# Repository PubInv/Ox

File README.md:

# NASA-COG

## Final Report

The final report delivered to NASA for this project can be [read here](https://drive.google.com/file/d/1jfJcSLfsybuC49I7llPhfTNI8ucRUW3h/view?usp=sharing).

## Introduction

This is a repo for a control system made for NASA to drive a Ceramic Oxygen Generation
technology they have developed. It was forked from ["The Ox"]() project of Public Invention run by Mr. Ben Coombs, which was in turn a fork of the VentOS project of Helpful Engineering let my Ben Coombs, Dr. Erich Schulz, and Robert L. Read.

However, the main reason we are starting with this fork is not that the Pressure Swing
Adsorption system of the Ox is a particularly relevant, but rather that the code
represents a nice platform of simple microcontroller control of related machines.

To wit, includes PlatformIO configuration, a state machine (finite automata),
a superloop architecutre, and a hardware abstraction layer.

This particular project of NASA will improve life support technology in space,
but may eventually greatly improve global health.

An unlisted [YouTube video](https://youtu.be/1nq-Mw7jZ5A) has been uploaded that shows this work in progress as of September, 2022.

## How to run

### Linux
The fundamental way to run this is to perform:  
> cd firmware  
> pio run -e native && ./.pio/build/native/program  
We are currently creating the [RibbonFish](https://github.com/PubInv/NASA-COG/blob/develop/RibbonFish.md) proof-of-concept.
This can be run on a Due by executing:  
> make pio-run-due_ribbonfish  
As this develops, it will use a specific Due hardware configuration,  
please see the [documentation](https://github.com/PubInv/NASA-COG/blob/develop/RibbonFish.md) for details to build your own.  

### Windows
With Visual Studio Code.  
Install the Plateform IO extention  
To open he project in Visual Studio Code.  
Open Project. Navigate to the firmware folder.   
Select the file platformio.ini  

## Annoyances

AFAIK, PlatformIO forces a directory tree depth of 5 levels.

This is not enough to organize the Hardware Abstraction Level they way I would prefer, forcing us to make some messy directories that are less than clear.

For example, to implement a Temperature Sensor, we would ideally have an
abstract (or virtual) implementation, a folder for real hardware,
and a folder for mock sensors.  I have no choice now but to jam
the mock sensors into the same directory with the real hardware and
use a naming convnention.

## The Command System

The NASA-COG system needs to allow the user to enter commands. The most obvious of these is "turn off".
Because the system should avoid thermal shocks, this is actually not simple.

We have previously used an [approach](https://github.com/PubInv/PIRCS-pubinv-respiration-control-standard) of using simple JSON objects to represent commands. We propose to use the same idea here, but obviously,
the command will be custom to the NASA-COG.

### Parameter Setting Commands
The general scheme is to use a JSON object like:

```JavaScript
{ "com": "T",
  "par": 7,
  "mod": "T",
  "val" : 732.3
  }
```

1. "com" is the command. For example, "T" can mean "set Temperature".
2. "par" is a parameter used to specify something about how to execute the command. For example, 7 could mean location 7, which might be between the 6th and 7th stack.
3. "mod" is a modifier of the command. For example, the "set Temperature" command could be used to
set the minimum, maximum, or the target temperature.
4. "val" is the value that is to be set.

For this problem space, we can specify some global parameters of the problem, some of which
involve safety. These can of course have default values "hard wired" into the code, but an
experimenter may wish to change these values (carefully).

1. The maximum rate of voltage change applied to a stack. Nominally we have defined this as 1 volt/second.
We have evidence that too rapid a voltage change (such as that caused by pulse-width modulation) can destroy
a stack.
2. The maximum rate of temperature change for a stack. Nominally we may say this as 2 degree K per minute,
which would allow the machine to reach operating temperature in 6 hours.
3. The maximum temperature difference across a stack in any dimenstion. We may not be able to control
this directly, but we can use it as a target.
4. The maximum voltage applied to a stack.
5. The maximum amperage applied to a stack.

### Event-like Commands

We will need other commands that represent discrete events in time. For example, each transition in the
state transition diagram below may be initiated by a command from the user (they may also occur
automatically due to an internal fault or even normal operation.)

We can implement particular commands with the same scheme.

For example, the simple object:

```JavaScript
{ "com": "C",
  "par": 0,
  "int": "s",
  "mod": "U",
  "val" : 0.0
  }
```

Could mean "Cool Down". The value "U" is used becasue the "mod" command is "unusued" in this case.

```JavaScript
{ "com": "W",
  "par": M,
  "int": "s",
  "mod": "U",
  "val" : 0.0
  }
```

In actual practice, these commands will be pasted into the serial port using either PlatformIO or the Arduino IDE.

Eventually, a user interface may be implemented that uses a knob or a nice webpage to enter commands.
However, by having each of these take only actions that can be implemented as such a command,
we bring discipline to the internal code.

## Actual Serial Commands

The serial port currently supports 6 one-character commands: w,c,e,a,i,o.
These mean:
1. warmup
2. cool down
3. emergency shutdown
4. acknowledge
5. idle
6. operate

Note: "acknowledge" means that the operator acknowledges that a critical
state has occurred and asserts it is okay to return to normal operation,
either because the problem as been removed or for some other reason.

Addtionally, the system supports "full commands", that look like this:

> { "com": "W", "par": "M", "int": "s", "mod": "U", "val" : 0.0 }

> { "com": "C", "par": "M", "int": "s", "mod": "U", "val" : 0.0 }

> { "com": "E", "par": "M", "int": "s", "mod": "U", "val" : 0.0 }

> { "com": "A", "par": "M", "int": "s", "mod": "U", "val" : 0.0 }

> { "com": "I", "par": "M", "int": "s", "mod": "U", "val" : 0.0 }

> { "com": "O", "par": "M", "int": "s", "mod": "U", "val" : 0.0 }

In fact, each "one character" command is a short hand for these commands.

The following format can be used to set parameters (P).
The three most important parameters are:
1. T : Temperature (in C) going into the stack
2. C : Current (in milliamps) going into the stack
3. F : Fan speed in RPM (we expect this to change to flow rate in SLM)
> { "com": "P", "par": "T", "int": "T", "mod": "U", "val" : 35 }

> { "com": "P", "par": "C", "int": "T", "mod": "U", "val" : 500 }

> { "com": "P", "par": "F", "int": "T", "mod": "U", "val" : 2000 }

These three commands set the:
1. Temperature into the stack to 35C
2. Set the Target current into the stack to 500 milliamps
3. Set the flow rate to 2000 ml/seconds

## License

In general we intend to follow the [Public Invention Licensed Guidelines](https://github.com/PubInv/PubInv-License-Guidelines) unless
NASA requests something different. If you are starting your own project, please
feel free to fork the license guidelines as a starting point if you like our
license policy.

This program includes free software: you can redistribute it and/or modify it under the terms of the GNU Affero General Public License as published by the Free Software Foundation, either version 3 of the License, or (at your option) any later version.

See the GNU Affero General Public License for more details. You should have received a copy of the GNU Affero General Public License along with this program. If not, see <https://www.gnu.org/licenses/>.

This program is distributed in the hope that it will be useful, but WITHOUT ANY WARRANTY; without even the implied warranty of MERCHANTABILITY or FITNESS FOR A PARTICULAR PURPOSE.

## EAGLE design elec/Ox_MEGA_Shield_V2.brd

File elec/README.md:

# Electrical Information on ODECOS Controler(s) and Plant(s)
PCB Connector Pin signal names, Due Signal Names, Chassis wiring and related information
Inverse cronological order

## Unit 3-???
A place holder for future work
See: TBD

## Unit 2
### Notes for creation of a new PCB  
This table pulls from information in the references 1 and 2.   
References:
1. Due Pin-Out Map for OEDCS1 : https://docs.google.com/spreadsheets/d/18wP1Cyg5-j3FP92x7no_JsCCFNvo9y2avyn5nvmAj6I/edit#gid=0
2. Fan Controller and Fan Wiring for OEDCS1: https://docs.google.com/document/d/1n3v-AxqNKEzcKqmHicGKnFmG8sKbNEL_pGaUlU9CZ8U/edit

   WARNING! At present pin D4 works without an external pull up resistor for the termocouples, but D5 does not; it requires an external pull up resistor
   Until we have time to rework our perf board, I am going to continue to use D4 for the MAX31850 OneWire interface.

#### Due Pin Wiring
| **Due Pin Number** 	| **Breakout** 	| **Signal Name** 	| **Set as I/O**   	| **Connection**                      	| **Notes**                             	|
|--------------------	|--------------	|-----------------	|------------------	|-------------------------------------	|---------------------------------------	|
| D0                 	| J6-2         	| NA              	| Input pullup.    	| None                                	| Not used                              	|
| D1                 	| J6-1         	| NA              	| Input pullup.    	| None                                	| Not used                              	|
| D2                 	| J6-3         	| NA              	| Input pullup.    	| None                                	| Not used                              	|
| D3                 	| J6-4         	| NA              	| Input pullup.    	| None                                	| Not used                              	|
| D4                 	| J6-5         	| SD ENABLE (BUT ALSO TEMP1) | Input pullup.    	| None                      	| SD CS on Ethernet card.               	|
| D5                 	| J6-6         	| TEMP1           	| BiDirection      	| Dallas 1 Wire / MAX31850K           	| Three daisy chained, requires 4.7k ohm pull up resistor (but D4 does not!) Please see note                   	|
| D6                 	| J6-7         	| NA              	| Input pullup.    	| None                                	| Not used                              	|
| D7                 	| J6-8         	| NA              	| Input pullup.    	| None                                	| Not used                              	|
| D8                 	| J7-1         	| NA              	| Input pullup.    	| None                                	| Not used                              	|
| D9                 	| J7-2         	| nFAN1_PWM       	| Output           	| Controlles transistor Q1            	| Was BLOWER_PWM                        	|
| D10                	| J7-3         	| NA              	| Input pullup.    	| None                                	| Not used                              	|
| D11                	| J7-4         	| NA              	| Input pullup.    	| None                                	| Not used                              	|
| D12                	| J7-5         	| NA              	| Input pullup.    	| None                                	| Not used                              	|
| D13                	| J7-6         	| NA              	| Input pullup.    	| None                                	| Not used                              	|
| D13                	| J7-6         	| NA              	| Input pullup.    	| None                                	| Not used                              	|
| D14                	| J2-1         	| NA              	|                  	| None                                	| Not used                              	|
| D15                	| J2-2         	| NA              	| Input pullup.    	| None                                	| Not used                              	|
| D16                	| J2-3         	| NA              	| Input pullup.    	| None                                	| Can be TX2                            	|
| D17                	| J2-4         	| NA              	| Input pullup.    	| None                                	| Can be RX2                            	|
| D18                	| J2-5         	| D_PSU_TX        	| UART1 TX         	| D_PSU_TX, R15 (then to Power Supply 	| TX1                                   	|
| D19                	| J2-6         	| D_PSU_RX        	| UART1 RX         	| D_PSU_RX, R14 (then to Power Supply 	| RX1                                   	|
| D20                	| J2-7         	| SDA             	| SDA              	| test point SDA1, R4, R13            	| SDA                                   	|
| D21                	| J2-8         	| SCL             	| SCL              	| test point SCL1, R2, R16            	| SCL                                   	|
| D22                	| J8-4         	| BLOWER_ENABLE   	| OUTPUT           	| R10                                 	| Enable Switched_Fan_Power at J15 9-12 	|
| D23                	| J8-3         	| NA              	| Input pullup.    	| None                                	| Not used                              	|
| D24                	| J8-6         	| NA              	| Input pullup.    	| None                                	| Not used                              	|
| D25                	| J8-5         	| NA              	| Input pullup.    	| None                                	| Not used                              	|
| D26                	| J8-8         	| NA              	| Input pullup.    	| None                                	| Not used                              	|
| D27                	| J8-7         	| NA              	| Input pullup.    	| None                                	| Not used                              	|
| D28                	| J8-10        	| NA              	| Input pullup.    	| None                                	| Not used                              	|
| D29                	| J8-9         	| NA              	| Input pullup.    	| None                                	| Not used                              	|
| D30                	| J8-12        	| NA              	| Input pullup.    	| None                                	| Not used                              	|
| D31                	| J8-11        	| NA              	| Input pullup.    	| None                                	| Not used                              	|
| D32                	| J8-14        	| nCS_GPAD        	| Output for nCS   	| R55, R61, Q5                        	| on 3.3 Volt                           	|
| D33                	| J8-13        	| TC_nCS1         	| Output for nCS   	| Thermocouple 1, R7                  	| on 3.3 Volt                           	|
| D34                	| J8-16        	| TC_nCS2         	| Output for nCS   	| Thermocouple 2, R3                  	| on 3.3 Volt                           	|
| D35                	| J8-15        	| TC_nCS3         	| Output for nCS   	| Thermocouple 3, R1                  	| on 3.3 Volt                           	|
| D36                	| J8-18        	| NA              	| Input pullup.    	| None                                	| Not used                              	|
| D37                	| J8-17        	| NA              	| Input pullup.    	| None                                	| Not used                              	|
| D38                	| J8-20        	| NA              	| Input pullup.    	| None                                	| Not used                              	|
| D39                	| J8-19        	| NA              	| Input pullup.    	| None                                	| Not used                              	|
| D39                	| J8-19        	| NA              	| Input pullup.    	| None                                	| Not used                              	|
| D40                	| J8-22        	| NA              	| Input pullup.    	| None                                	| Not used                              	|
| D41                	| J8-21        	| NA              	| Input pullup.    	| None                                	| Not used                              	|
| D42                	| J8-24        	| NA              	| Input pullup.    	| None                                	| Not used                              	|
| D43                	| J8-23        	| NA              	| Input pullup.    	| None                                	| Not used                              	|
| D44                	| J8-26        	| NA              	| Input pullup.    	| None                                	| Not used                              	|
| D45                	| J8-25        	| NA              	| Input pullup.    	| None                                	| Not used                              	|
| D46                	| J8-28        	| NA              	| Input pullup.    	| None                                	| Not used                              	|
| D47                	| J8-27        	| NA              	| Input pullup.    	| None                                	| Not used                              	|
| D48                	| J8-30        	| NA              	| Input pullup.    	| None                                	| Not used                              	|
| D49                	| J8-29        	| NA              	| Input pullup.    	| None                                	| Not used                              	|
| D50                	| J8-32        	| NA              	| Input pullup.    	| None                                	| Not used                              	|
| D51                	| J8-31        	| SSR_PWM         	| OUTPUT           	| R9                                  	| Active High.                          	|
| D52                	| J8-34        	| NA              	| Input pullup.    	| None                                	| Not used                              	|
| D53                	| J8-33        	| NA              	| Input pullup.    	| None                                	| Not used                              	|
| SDA1               	| J7-9         	| NA              	| Input pullup.    	| None                                	| Not used                              	|
| SCL1               	| J7-10        	| NA              	| Input pullup.    	| None                                	| Not used                              	|
| CANR               	| J4-7         	| NA              	| Input pullup.    	| None                                	| Not used                              	|
| CANT               	| J4-8         	| NA              	| Input pullup.    	| None                                	| Not used                              	|
| DAC0               	| J4-5         	| Disable         	| Only Output      	| None                                	| Not used                              	|
| DAC1               	| J4-6         	| Disable         	| Only Output      	| None                                	| Not used                              	|
| A0                 	| J5-1         	| BLOWER_TACH     	| Input pullup.    	| R11                                 	| Measure RPM                           	|
| A1                 	| J5-2         	| NA              	| Input pullup.    	| None                                	| Not used                              	|
| A2                 	| J5-3         	| NA              	| Input pullup.    	| None                                	| Not used                              	|
| A3                 	| J5-4         	| NA              	| Input pullup.    	| None                                	| Not used                              	|
| A4                 	| J5-5         	| NA              	| Input pullup.    	| None                                	| Not used                              	|
| A5                 	| J5-6         	| NA              	| Input pullup.    	| None                                	| Not used                              	|
| A6                 	| J5-7         	| NA              	| Input pullup.    	| None                                	| Not used                              	|
| A7                 	| J5-8         	| NA              	| Input pullup.    	| None                                	| Not used                              	|
| A8                 	| J4-1         	| NA              	| Input pullup.    	| None                                	| Not used                              	|
| A9                 	| J4-2         	| NA              	| Input pullup.    	| None                                	| Not used                              	|
| A9                 	| J4-2         	| NA              	| Input pullup.    	| None                                	| Not used                              	|
| A10                	| J4-3         	| NA              	| Input pullup.    	| None                                	| Not used                              	|
| A11                	| J4-4         	| NA              	| Input pullup.    	| None                                	| Not used                              	|
| AREF               	| J7-8         	| NA              	| From DUE         	| None                                	| Not used                              	|
| nRST1              	| J3-6         	| NA              	| Pulled up on DUE 	| None                                	| Not used                              	|
| IOREF              	| J3-7         	| NA              	| NA               	| None                                	| Not used                              	|
| VIN                	| J3-1         	| VIN             	| NA               	| +12V into this pin through R76      	|                                       	|
| +5V                	| J3-4         	| VIN+5V          	| NA               	| Power from Due voltage regulator    	| Three pins.                           	|
| 3.3V               	| J3-5         	| 3.3V            	| NA               	| Power from Due voltage regulator    	| One pin.                              	|
| MISO               	| tp CPIO1     	| CIPO            	| Input            	| SPI bus                             	|                                       	|
| MOSI               	| tp COPI      	| COPI            	| Output           	| SPI bus                             	|                                       	|
| SCK                	| tp SPI_SCK   	| SPI_SCK         	| Output           	| SPI bus                             	|                                       	|
| nRST2              	| NA           	| SPI_nRST        	| Input            	| S1 reset switch                     	|                                       	|
| end                	|              	|                 	|                  	|                                     	|                                       	|  

**Ethernet pin usage:**
Pins usage on Arduino
* D4: SD card chip select
* D10: W5200 Chip Select
* D11: SPI MOSI
* D12: SPI MISO
* D13: SPI SCK

### Chassis Wiring of ODECOS Unit 2.
Diagram(s) here...

## Unit 1
Wiring of ODECOS Unit 1 Notes
1. Due Pin-Out Mape for OEDCS1 : https://docs.google.com/spreadsheets/d/18wP1Cyg5-j3FP92x7no_JsCCFNvo9y2avyn5nvmAj6I/edit#gid=0
2. Fan Controller and Fan Wiring for OEDCS1: https://docs.google.com/document/d/1n3v-AxqNKEzcKqmHicGKnFmG8sKbNEL_pGaUlU9CZ8U/edit

Wiring of thermocouple amplifires

Revisions:
* 20230821, Update DB25 Male 2-5 from +12V to "+24V Switched (fans)"

| Fan Breakout 	| Signal-Function   	| DB25 MALE Pin # 	| DB25 FEMALE Pin # 	| Other 	| Due Pin 	| Due Signal 	|
|--------------	|-------------------	|-----------------	|-------------------	|-------	|---------	|------------	|
| 1            	| +24V Switched (fans) 	| 2-5             	| 9-12              	|       	| ???      	| FAN_POWER         	|
| 2            	| GND for all fans  	| 22-25           	| 14-17             	|       	| GND     	| NA         	|
| 3            	| #1 PWM            	| 13              	| 1                 	| J10-1 	| D9      	| nFAN1_PWM  	|
| 4            	| #1 Tach           	| 9               	| 5                 	| J9-1  	| A0      	| FAN1_FG    	|
| 5            	| #2 PWM            	| 12              	| 2                 	| J10-2 	|         	| nFAN2_PWM  	|
| 6            	| #2 Tach           	| 8               	| 6                 	| J9-2  	|         	| FAN2_FG    	|
| 7            	| #3 Tach           	| 11              	| 3                 	| J10-3 	|         	| nFAN3_PWM  	|
| 8            	| #3 PWM            	| 7               	| 7                 	| J9-3  	|         	| FAN3_FG   	|
| 9            	| #4 Tach           	| 10              	| 4                 	| J10-4 	|         	| nFAN4_PWM  	|
| 10           	| #4 PWM            	| 6               	| 8                 	| J9-4  	|         	| FAN4_FG   	|
|              	|                   	|                 	| 25                	| J11-3 	|         	|            	|
|              	|                   	|                 	| 13                	| J11-4 	|         	|            	|
|              	|                   	|                 	| 18                	| J12-1 	|         	|            	|
|              	|                   	|                 	| 19                	| J12-2 	|         	|            	|
|              	|                   	|                 	| 20                	| J12-3 	|         	|            	|
|              	|                   	|                 	| 21                	| J12-4 	|         	|            	|
|              	|                   	|                 	| 22                	| J12-5 	|         	|            	|
|              	|                   	|                 	| 23                	| J12-6 	|         	|            	|
|              	|                   	|                 	| 24                	| J12-7 	|         	|            	|

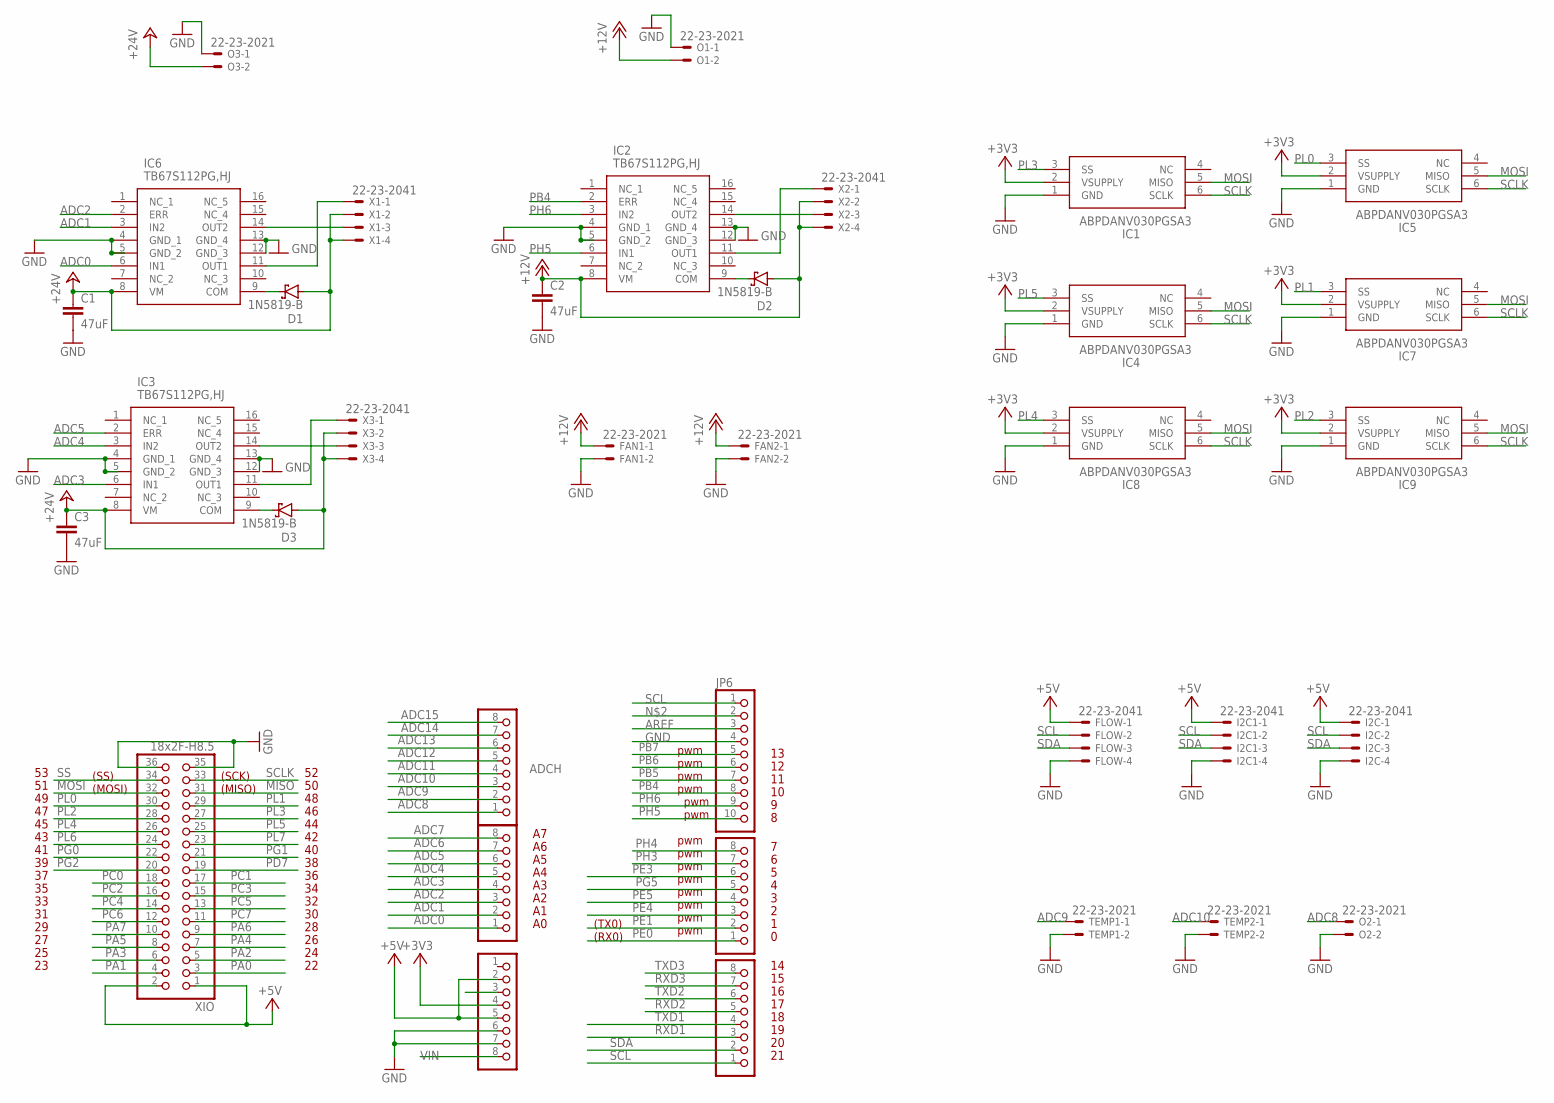
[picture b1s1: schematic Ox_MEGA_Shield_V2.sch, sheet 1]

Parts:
ADCH: FH254-108DF08500V; 1X08
ADCL: FH254-108DF08500V; 1X08
C1, C2, C3: 47uF; C2.5-3
COMMUNICATION: FH254-108DF08500V; 1X08
D1, D2, D3: 1N5819-B; DO41-7.6
FAN1, FAN2: 22-23-2021
FLOW: 22-23-2041
I2C, I2C1: 22-23-2041
IC1, IC4, IC5, IC7, IC8, IC9: ABPDANV030PGSA3
IC2, IC3, IC6: TB67S112PG,HJ; DIP762W60P254L1975H445Q16N
JP6: FH254-110DF08500V; 1X10
O1, O2, O3: 22-23-2021
POWER: FH254-108DF08500V; 1X08
PWML: FH254-108DF08500V; 1X08
TEMP1, TEMP2: 22-23-2021
X1, X2, X3: 22-23-2041
XIO: 18x2F-H8.5; 2X18

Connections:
+3V3: IC1.2 (VSUPPLY), IC4.2 (VSUPPLY), IC5.2 (VSUPPLY), IC7.2 (VSUPPLY), IC8.2 (VSUPPLY), IC9.2 (VSUPPLY), POWER.4
+5V: FLOW.1, I2C.1, I2C1.1, POWER.2, POWER.5, XIO.1, XIO.2
+12V: C2.1, D2.A, FAN1.1, FAN2.1, IC2.8 (VM), O1.2, X2.2, X2.4
+24V: C1.1, C3.1, D1.A, D3.A, IC3.8 (VM), IC6.8 (VM), O3.2, X1.2, X1.4, X3.2, X3.4
ADC0: ADCL.1, IC6.6 (IN1)
ADC1: ADCL.2, IC6.3 (IN2)
ADC2: ADCL.3, IC6.2 (ERR)
ADC3: ADCL.4, IC3.6 (IN1)
ADC4: ADCL.5, IC3.3 (IN2)
ADC5: ADCL.6, IC3.2 (ERR)
ADC6: ADCL.7
ADC7: ADCL.8
ADC8: ADCH.1, O2.1
ADC9: ADCH.2, TEMP1.1
ADC10: ADCH.3, TEMP2.1
ADC11: ADCH.4
ADC12: ADCH.5
ADC13: ADCH.6
ADC14: ADCH.7
ADC15: ADCH.8
AREF: JP6.3
GND: C1.2, C2.2, C3.2, FAN1.2, FAN2.2, FLOW.4, I2C.4, I2C1.4, IC1.1 (GND), IC2.4 (GND_1), IC2.5 (GND_2), IC2.12 (GND_3), IC2.13 (GND_4), IC3.4 (GND_1), IC3.5 (GND_2), IC3.12 (GND_3), IC3.13 (GND_4), IC4.1 (GND), IC5.1 (GND), IC6.4 (GND_1), IC6.5 (GND_2), IC6.12 (GND_3), IC6.13 (GND_4), IC7.1 (GND), IC8.1 (GND), IC9.1 (GND), JP6.4, O1.1, O2.2, O3.1, POWER.6, POWER.7, TEMP1.2, TEMP2.2, XIO.35, XIO.36
MISO: XIO.31
MOSI: IC1.5 (MISO), IC4.5 (MISO), IC5.5 (MISO), IC7.5 (MISO), IC8.5 (MISO), IC9.5 (MISO), XIO.32
unnamed: IC6.14 (OUT2), X1.3
unnamed: IC2.11 (OUT1), X2.1
unnamed: IC6.11 (OUT1), X1.1
unnamed: D2.C, IC2.9 (COM)
unnamed: IC3.14 (OUT2), X3.3
unnamed: D1.C, IC6.9 (COM)
unnamed: IC2.14 (OUT2), X2.3
unnamed: D3.C, IC3.9 (COM)
unnamed: IC3.11 (OUT1), X3.1
PA0: XIO.3
PA1: XIO.4
PA2: XIO.5
PA3: XIO.6
PA4: XIO.7
PA5: XIO.8
PA6: XIO.9
PA7: XIO.10
PB4: IC2.2 (ERR), JP6.8
PB5: JP6.7
PB6: JP6.6
PB7: JP6.5
PC0: XIO.18
PC1: XIO.17
PC2: XIO.16
PC3: XIO.15
PC4: XIO.14
PC5: XIO.13
PC6: XIO.12
PC7: XIO.11
PD7: XIO.19
PE0: PWML.1
PE1: PWML.2
PE3: PWML.6
PE4: PWML.3
PE5: PWML.4
PG0: XIO.22
PG1: XIO.21
PG2: XIO.20
PG5: PWML.5
PH3: PWML.7
PH4: PWML.8
PH5: IC2.6 (IN1), JP6.10
PH6: IC2.3 (IN2), JP6.9
PL0: IC5.3 (SS), XIO.30
PL1: IC7.3 (SS), XIO.29
PL2: IC9.3 (SS), XIO.28
PL3: IC1.3 (SS), XIO.27
PL4: IC8.3 (SS), XIO.26
PL5: IC4.3 (SS), XIO.25
PL6: XIO.24
PL7: XIO.23
RESET: POWER.3
RXD1: COMMUNICATION.3
RXD2: COMMUNICATION.5
RXD3: COMMUNICATION.7
SCL: COMMUNICATION.1, FLOW.2, I2C.2, I2C1.2, JP6.1
SCLK: IC1.6 (SCLK), IC4.6 (SCLK), IC5.6 (SCLK), IC7.6 (SCLK), IC8.6 (SCLK), IC9.6 (SCLK), XIO.33
SDA: COMMUNICATION.2, FLOW.3, I2C.3, I2C1.3
SS: XIO.34
TXD1: COMMUNICATION.4
TXD2: COMMUNICATION.6
TXD3: COMMUNICATION.8
VIN: POWER.8

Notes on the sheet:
pwm
(TX0)
(RX0)
(SS)
(MOSI)
(SCK)
(MISO)

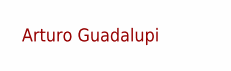
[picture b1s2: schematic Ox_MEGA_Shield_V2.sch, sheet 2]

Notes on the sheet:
Arturo Guadalupi

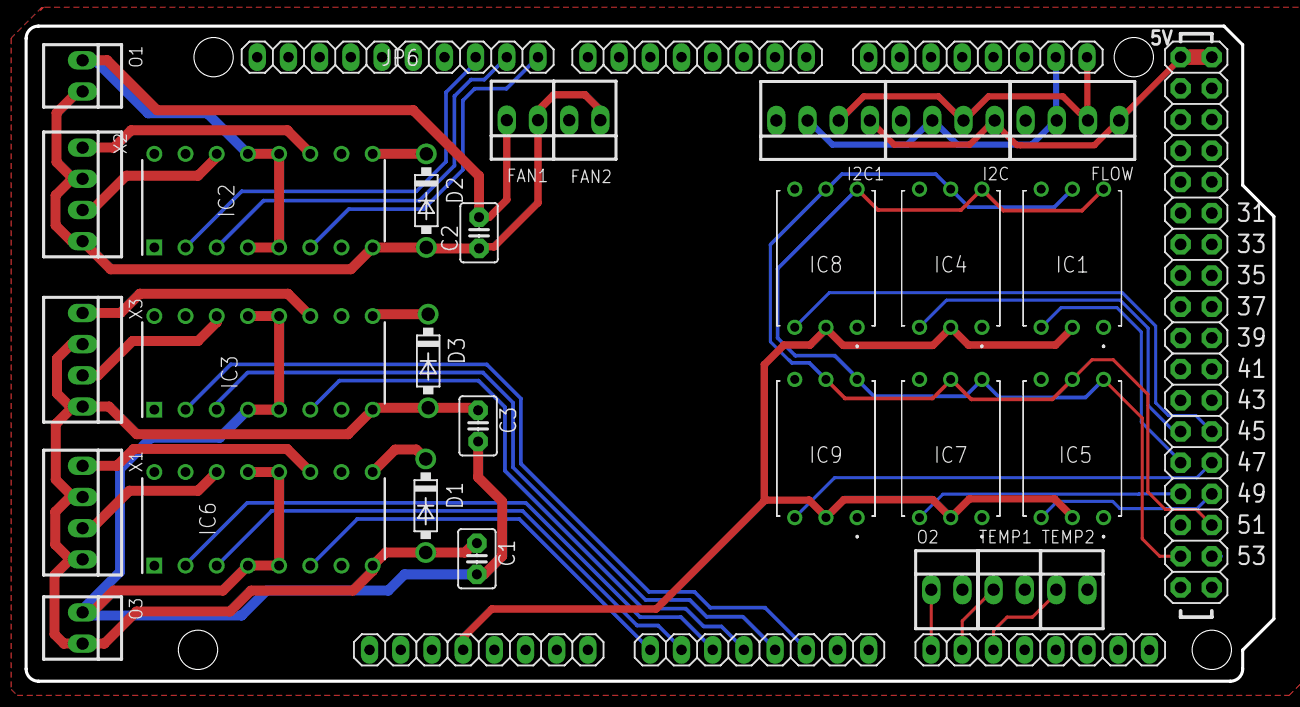
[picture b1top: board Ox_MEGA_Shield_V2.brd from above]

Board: 2 copper layers, 101.6 x 53.3 mm, 35 parts (0 on the bottom side), 36 nets.

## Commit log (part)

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2023-08-17 Add U1 rack mount on right.
2023-08-17 Add a multitransform but it overwrites other features and DB9 has dependancy cycle and not recompute.
2023-08-17 Update README.md
    Add the OEDCS1-Aug-17.JPG image to the README.md at mech/enclosure/AssemblyPhotos
2023-08-17 imported Lee's changed inputs into the folder Control Board,
    Also added in Robert's pin labels
    ToDo: clean up broken links, and import in the layout files from Lee's project
    Clean up the fan control pinout, the DB25 is a bit of a mess
    consider using IDC to DB25 connectors for ease of assembly and installation.
2023-08-18 Add Lees PublicInvention submodule library. Update Control V1 project and schematic for new library.
2023-08-19 Rename Due CFC Pinouts to Due CFC Pinouts.md
2023-08-19 Update README.md
    Add wiring of thermocouple amplifiers of Unit 1.
2023-08-21 Update README.md
    Update fan supply voltage and indicated switched.
2023-08-21 Switch to FAN POWER.
2023-08-21 Update README.md
    Fix, swap, function on DB25 pins 3 and 7
2023-08-21 Add net names to fan controler block.
2023-08-22 Update README.md
    Add links for On line schematic viewing from **Kicanvas** of the current schematics.
2023-08-22 Add fan circuits. Add thermocouple interface circuits.
2023-08-23 fixing a bug in the data logging, seems to be working now
2023-08-23 Add footrpint to Max31850 module.
2023-08-24 debugged getting the fan test working again
2023-08-24 Add footprints for thermoucouple modules to schematic and PCB. This commit does NOT capture the library changes.
2023-08-24 Flip the front panel around.
2023-08-24 fan is now working properly
2023-08-24 Update schematic for MCP9600 I2C thermocouple.
2023-08-25 Next and place thermocouple boards.
2023-08-25 Fix swome ERC errors.
2023-08-25 Add header sockets. Refine PCB placement, temprature sensors.
2023-08-26 Update README.md
    Begin Due Pin Wiring Table
2023-08-27 very significant rewrite and simplication of the main algorithms
2023-08-27 Update README.md
    Add more details to Due wiring table. Up to D19.
2023-08-27 Net name congruancy to D35. Add named test points.
2023-08-27 Update README.md
    Finish the Due pin table.
2023-08-27 Update README.md
    Update of Due Pin Number table resolving some "???" and more.
2023-08-28 Update README.md
    Update to Due pin wiring after team review.
2023-08-28 Changes during team review.
2023-08-28 Lots of routing. Lots remaining.
2023-08-28 Finishe routing on enlarged perimeter.
2023-08-28 fixing bug #148 by inceasing MAX_TASKS and some other improvements
2023-08-28 using sentinel numbers in report
2023-08-29 Fixing bug #175
2023-08-30 Update parts in schematic for BOM generation.
2023-08-30 Add BOM spread sheet and a JLCPCB BOM.
2023-08-30 Update README.md
    Update the Control v1 README.md with KICanvas link to the PCB
2023-08-30 Add footprints to KiCad board. Make simple Due and Ethernte boards for pullin into FreeCAD assembly and do so.
2023-08-30 Preparation for the stage2 heater code
2023-08-30 changing obsolete file name
2023-08-30 further refactoring of state machine
2023-08-31 significant refactoring to make Stage2 heater
2023-08-31 stage2 report working now
2023-08-31 Update README.md
    Make more descriptive of the scope of the content.
2023-08-31 Add folder and a README.md for capture of Serial number 2 fabrication.
2023-08-31 Update README.md
    Add more information about serial number 2 build.
2023-08-31 some progress on Stage2 desgin
2023-09-01 debugging of stage2 related code
2023-09-02 working mostly on improving ability to survive resets and other debugging
2023-09-03 some more refacotrings (no build attempted yet
2023-09-03 now the heater code compiles
2023-09-04 checking if isinf on ohms values to avoid string being printed and messing up Cumulocity
2023-09-04 Update README.md
    Add the acronym OEDCS with the explanation.
2023-09-04 removing intermediate directories that we used for passing code but are now breaking the build on Windows machines (or maytbe all)
2023-09-05 Remove submodult to Watchdog example code.
2023-09-05 in middle of debuggin, stacks[0] point on COG_HAL appears to be incorrect by the time it used
2023-09-05 Update Stage2_Heater.md
    added ethernet shield pin references for SPI
2023-09-06 Add imaes of Controller V1 PCB and Assys from JLCPCB.
2023-09-06 Add a Controller support bracket.
2023-09-06 Update README.md
    With PWA
2023-09-06 fixed majore bug that was preventing the addition of the ramp up time
2023-09-06 Image Making print out more accurate.
2023-09-06 Create README.md
    Describe the files.
2023-09-07 turning off debugging statments
2023-09-07 Update Watchdog to rev 6. Save to flash only when D12 low. Increment flash count on reset. Add serial number to structure.
2023-09-08 Change PCB gap on ControllerSupport from 1mm to 2mm.
2023-09-09 Update README.md
    Spaces to format better.
2023-09-11 Create networking
2023-09-12 Changing from D4 to D5 for temperature reads
2023-09-12 Incrementing version for change in thermocouple pin.
2023-09-13 added stage2 hal changes
2023-09-13 adding target fore due_stage2_heater
2023-09-13 intermediate files, not compiling
2023-09-13 compiling, but untested
2023-09-13 committing some debugging statements
2023-09-13 Update Stage2_Heater.md
    updated pinout docs
2023-09-14 OnePinHeater refactoring, changes to makefile
2023-09-14 major refactoring of network code to remove it from tha task and put it in the hal
2023-09-14 Adding two files
2023-09-14 creatign Stage2 Network class
2023-09-14 refactoring file names
2023-09-14 Add files via upload
    Full resolution Serial number 2 photographs.
2023-09-15 fix networking code
2023-09-15 fix W5x00 init error message
2023-09-15 adding immature test program that does not seem to have any bad readings even with fan on
2023-09-15 revving version number
2023-09-16 beginning of the 5-knob work
2023-09-16 Update README.md
    Add more MAC addresses
2023-09-16 initial checkin, reading commands but commands do nothing, this branch is broken for now
2023-09-16 Some bugs from 263 fixed, but Network may not be working.
2023-09-16 some improvements
2023-09-17 intermediate waypoint
2023-09-17 Update state_machine_manager.cpp
    enabled ramp down target temp, otherwise computeRampDnTargetTemp returns float t unmodified
2023-09-17 signifianct work, and some realizations for simplifications
2023-09-18 fix memory leaks inside parsing state params and phases
2023-09-18 adding DueFlashStorage library
2023-09-18 adding wattage limitation
2023-09-18 Update README.md
    Link to an issue for how to find an ODECS IP address.
2023-09-18 Create README.md
    Description of Files / Folders
2023-09-18 latest
2023-09-19 removing param script retrieval
2023-09-19 providing a back door for testing when you don't have 3 thermocouples as a compile time switch
2023-09-19 change generation of max address to set last bit 0 for cfc and 1 for stage2
2023-09-19 revert my last change
2023-09-20 minor udp fix
2023-09-20 intermediate code, unknown state
2023-09-20 Update README.md
    Add MAC for OEDCS Serial number 2.
2023-09-20 moving back to 3.11.0 for Dallas OneWire
2023-09-20 reveting to use standard thermocooples for Stage2
2023-09-21 removing stray debugging statements
2023-09-21 fixing but with temperature jump
2023-09-22 fixing global start temperature bug
2023-09-22 Fixing an incorrect variable, passing GLOBAL_RECENT_TEMP when it should have been WARM_UP_BEGIN_TIME, cause ramp up to be too high
2023-09-22 update to debugging
2023-09-22 Add Due mechanical files. Add step for the Due Ethernet Control v1 assembly.
2023-09-22 compatability with SPI thermocouple boards and to ensure there is always an initial good read before compair
2023-09-23 Update Fan 4-wire cable interface
2023-09-26 Improving Make Target
2023-09-27 now compiles Stage2Heater code successfully
2023-09-27 changing precision of printed value
2023-09-27 Add simulation file and result as PNG.
2023-09-27 Update README.md
    Add a README.md to explain the simulation and simulation files.
2023-09-27 Update platformio.ini
    added support for rPi needs to have arm compiler defined
    per
    https://github.com/platformio/platform-ststm32/issues/404#issuecomment-673693211
2023-09-27 Update README.md
    Correct some novel spelling.
    Improve formatting of notes.
    Add description of limitation of the simulation.
2023-09-28 Add a simulation workbook to RCRC simulation.
2023-09-28 Update README.md
    Update with link to this schematic.
2023-09-28 changing PID Tunings
2023-10-02 Update polarity of connections to the GPOLY to correct the signs of the terms in the output.
2023-10-04 improve casting in TC toleration time math and fixing major bug in the use of the PID controller.
2023-10-05 adding debugging to the test program by using a fork with more
2023-10-06 Create README.md
    Add markdown with previews of photos.
2023-10-06 Update README.md
    Add link to folder of OEDCS Serial number 1 device photos.
2023-10-07 Update for JLCPCB part number of J10
2023-10-10 Copy PCB version 1.0 to version 1v1 and delete stale files. No other changes.
2023-10-10 Fix J10 backwards.
2023-10-11 Place many of new components. Still need to place SSR parts.
2023-10-11 Update README.md
    Update most of the PCB information. THIS PCB is not yet finished.
2023-10-11 Added schematic components for display header
2023-10-11 cosmetic schematic layouc changes
2023-10-11 Add power supply enable circuits. Add shutdown button.
2023-10-12 Make first cut JLCPCB BOM.
2023-10-12 unified 1R and 1R0 references
2023-10-12 Update README.md
    Add display_interface.kicad_sch to the README.MD
2023-10-12 Create Safety and Hazards Failure Effects Mode Analysis
2023-10-13 Some component placement for display and I2C.
2023-10-13 Still working on a few JLCPCB part numbers for components, headers - sockets.
2023-10-13 Fill ground.
2023-10-13 Getting close to order of PWAs for Control 1v1.
2023-10-13 Add the files JLCPCB modified for their order process.
2023-10-13 Add Breadboard30P.
2023-10-16 Add the Manufacturing files and notes as used for the JLCPCB order on 20231016,
2023-10-17 Holes in flanges but they disappear.
2023-10-17 Changes to change headders to sockets. Scockets for thermcouple amplifiers.
2023-10-17 updated manufacturing bom and positino files
2023-10-18 A 3D file for the Control V1 printed wiring assembly.
2023-10-18 Update README.md
    Update screen shot of 3D view of Control V1.1 PWA.
2023-10-18 Add holes to Front Panel, but not yet located fully.
2023-10-18 Add center holes to flanges and to Front Panel.
2023-10-18 Create README.md
    A read me for the 2U enclosure drawings.
2023-10-19 Add an IP64 M12 Bulkhead to wire for I2C pressue sensor.
2023-10-19 Add the TwoU_Assembly_TwinPower.FCStd drawing.
2023-10-19 Adding arduino test code for display and heater
2023-10-19 Add initial files for heartbeat task.
2023-10-19 Heartbeat task toggeling LED_BUILTIN
2023-10-19 Make a constant for the Heartbeat period.
2023-10-20 Increment version to Rev: 0.3.9, add new files for power_monitor_task. Compiles but does nothing.
2023-10-20 Power monitor task measuring SENSE_24V and reporing it as voltage and reporting power good or bad.
2023-10-21 Add TYSETC enclosure for BigTreeTech display and place on front panel of TwoU.
2023-10-23 Call a power monitor function in CogTask::_run(). Made duplicate function in cog_task.cpp.
2023-10-24 added new task to periodically log the state of the machine seperately from other tasks
2023-10-24 adding new function
2023-10-27 verified log recordings work
2023-10-27 Update debug.h
    fix hang when building on arm
2023-11-06 Rearrange heat source and RC elements for clarity.
2023-11-09 Create SBC setup instructions
2023-11-10 initial pcb design for high current, constant current psu
2023-11-13 added both proposed and development configuartion
2023-11-13 updated SBC setup instructions
2023-11-15 Added a set function to change period of a task
    Fixed a few bugs and typos
    Added logRecorderTask pointer to MachineState and added function calls to SetPeriod for
    Critical Fault and Emergency Shutdown to increase the periodicity of the reporting.
    possibly should add a dedicated function to call the logging function on state transitions.
